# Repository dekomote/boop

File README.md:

# Boop

A small board that lets ESPHome press the power and reset buttons on a PC, and tell whether the PC is actually on.

<div style="text-align: center;">

</div>

It carries a Seeed XIAO ESP32-C3 on sockets. Two relays sit in parallel with the
front-panel power and reset buttons, so the real buttons keep working. A third
input watches the power LED header so Home Assistant knows the state instead of
guessing.

<div style="text-align: center;">

</div>

**Status:** designed and checked (ERC clean, DRC has no errors, JLCPCB's
pre-flight passes). The first board has been built and soldered, and it works.

## How it works

```
D2 (GPIO4) -> 150R -> opto -> relay K1 -> in parallel with the PWR button
D3 (GPIO5) -> 150R -> opto -> relay K2 -> in parallel with the RESET button
D1 (GPIO3) <- opto <- motherboard PWR LED header (low = PC is on)
```

- Each relay coil is switched by an LTV-817S opto (rank D, so there is enough
  gain to drive a 23 mA coil) with a 1N4148W flyback diode.
- The LED sense side is an opto with a 470R series resistor and a 10k pull-up to
  3V3. A small diode across its LED protects it if the wires are swapped.
- The board is fed 5 V either from the motherboard USB header (through a
  Schottky, so nothing flows back into the PC) or from the XIAO's own USB-C. If
  both are connected the higher one wins. One thing to avoid: the XIAO's 5 V pin
  is wired straight to USB VBUS, so if the header feeds the board while the
  USB-C is plugged into a computer that is switched off, the board pushes 5 V
  into that computer's port. Unplug the USB-C when you are done flashing.

Heads up: for the PC to be startable from off, the motherboard USB 5 V has to stay
alive in shutdown. Many boards turn it off unless you enable something like "USB
standby power" or disable ErP in the BIOS. If yours cuts it, power the board
from the USB-C instead.

## Connectors

All the 2-pin headers are 2.54 mm. The left column is always the motherboard
side and the right column is always the case side, so it is the same on every
pair.

| Ref | Label | Goes to |
|-----|-------|---------|
| J1  | 5V IN | JST XH 2-pin, `+` and `-` are marked. Optional 5 V from the motherboard USB header (pin 1 VCC, pin 7 GND) |
| J2  | PWR SW / MB | motherboard power switch header |
| J3  | PWR SW / CASE | the case power button lead |
| J4  | RST SW / MB | motherboard reset header |
| J5  | RST SW / CASE | the case reset button lead |
| J8  | PWR LED / MB | motherboard power LED header, `+` marked |
| J9  | PWR LED / CASE | the case power LED lead, `+` marked |
| J6, J7 | XIAO | 1x7 female sockets, pin names are printed on the board |

The relay contacts are volt-free, so polarity on the button headers does not
matter. The LED pair does have a polarity, follow the `+`.

Four M3 holes in the corners for standoffs.

## ESPHome

The full config is in [`boop-esphome.yaml`](boop-esphome.yaml). Pins are the XIAO
ESP32-C3 D-numbers: D1 = GPIO3, D2 = GPIO4, D3 = GPIO5.

It exposes three buttons to Home Assistant (power tap, power hold for force off,
reset) and a "PC is on" sensor. The relays are internal and always start off, so
a reboot can't hold a button down.

Create a `secrets.yaml` next to it with `wifi_ssid`, `wifi_password`,
`boop_api_key` (`openssl rand -base64 32`), `boop_ota_password` and
`boop_ap_password`, then flash the first time over USB:

```
esphome run boop-esphome.yaml
```

If the board isn't detected, hold BOOT, tap RESET, release BOOT. Unplug J1
(the motherboard 5 V) while flashing over USB-C. Later updates go over Wi-Fi.

## Building it

Everything you need for JLCPCB is in `fab/`.

## Things worth knowing

- The XIAO ESP32-C3 uses an external antenna. A metal PC case eats Wi-Fi, so
  route the antenna out of the case.
- The relays are the 4.5 V coil version (G6K-2F-Y DC4.5), on purpose. The coil
  only sees the 5 V rail minus the Schottky drop and the opto's saturation
  voltage, which is about 4.0 to 4.3 V at the USB minimum of 4.75 V (the opto's
  saturation voltage at 20-odd mA is not in the datasheet, I assumed 0.2 to
  0.4 V from the curves). A 5 V coil needs 4.0 V to pull in, which is too thin;
  the 4.5 V one pulls in at 3.6 V. Worth measuring the coil voltage on the first
  board.

## Licence

Copyright 2026 Dejan Noveski. Released under
[CC BY-SA 4.0](https://creativecommons.org/licenses/by-sa/4.0/), the full text
is in `LICENSE`. In plain words: build it, sell it, change it, as long as you
credit me and share your changes under the same licence. That covers the
schematic, the board, the Gerbers, the script and the ESPHome example.

The exception is `lib/`, which holds trimmed copies of KiCad's stock libraries.
Those keep their own licence, see `lib/NOTICE.md`.

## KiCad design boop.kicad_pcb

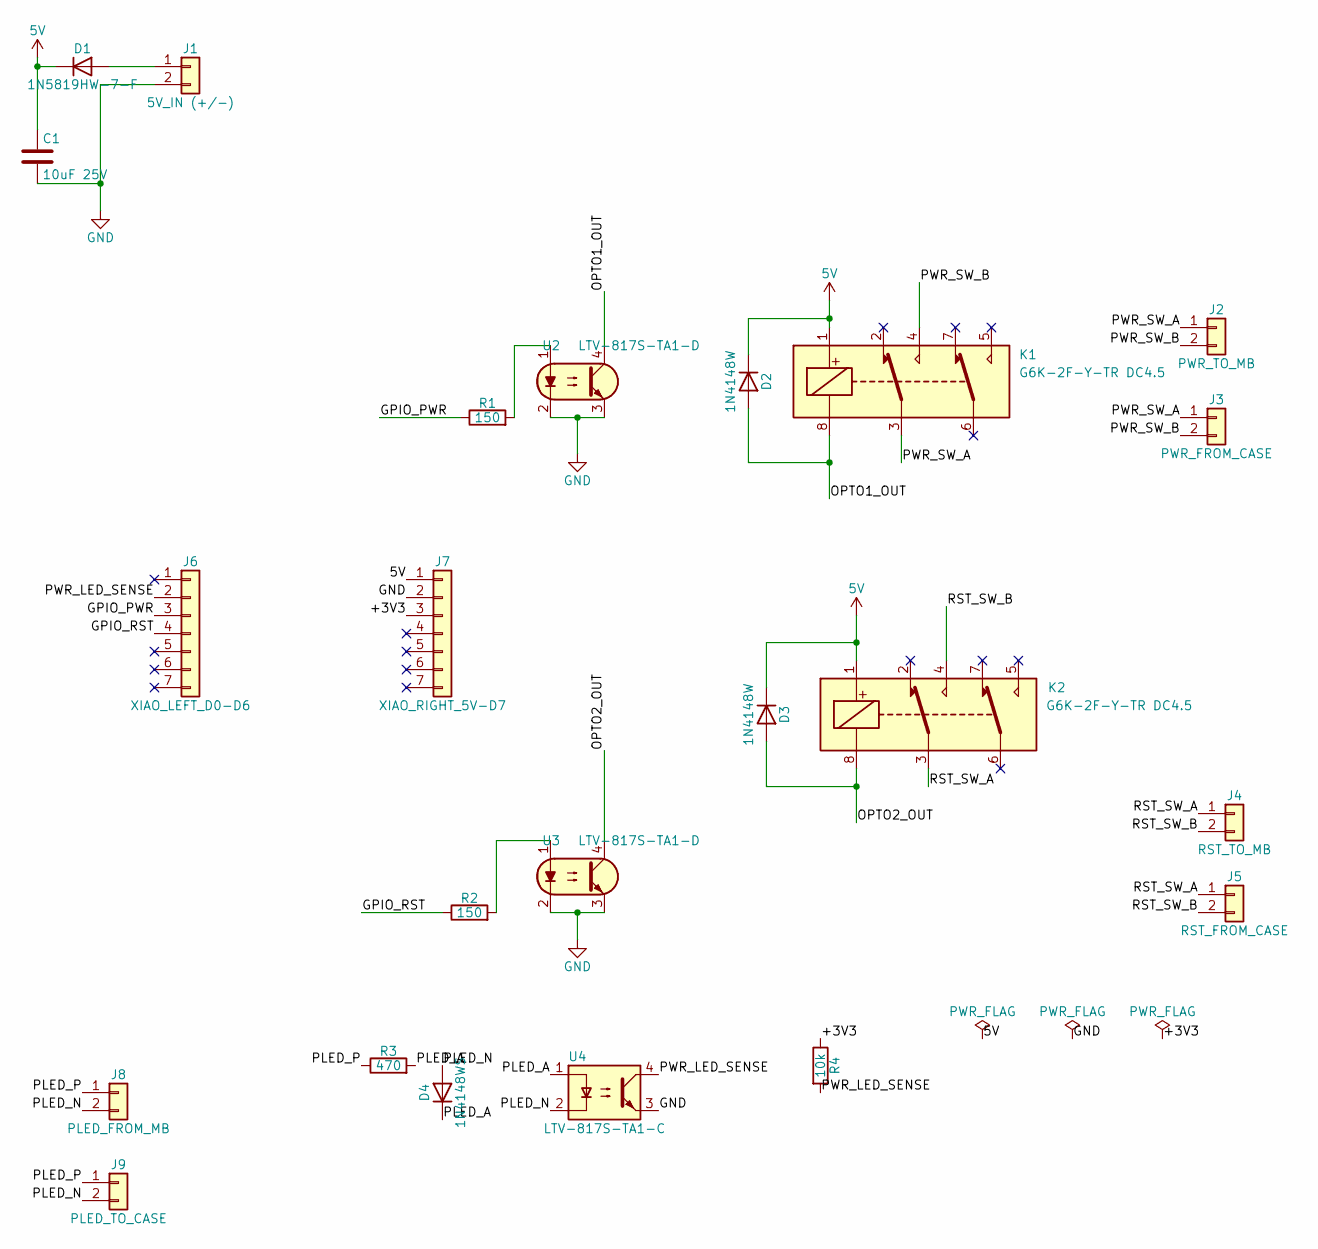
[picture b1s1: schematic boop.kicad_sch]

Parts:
C1: 10uF 25V; C_1206_3216Metric; LCSC C9807
D1: 1N5819HW-7-F; D_SOD-123; LCSC C82544
D2, D3: 1N4148W; D_SOD-123; LCSC C2099
D4: 1N4148WS; D_SOD-323; LCSC C2128
J1: 5V_IN (+/-); JST_XH_B2B-XH-A_1x02_P2.50mm_Vertical; LCSC C158012
J2: PWR_TO_MB; PinHeader_1x02_P2.54mm_Vertical; LCSC C492401
J3: PWR_FROM_CASE; PinHeader_1x02_P2.54mm_Vertical; LCSC C492401
J4: RST_TO_MB; PinHeader_1x02_P2.54mm_Vertical; LCSC C492401
J5: RST_FROM_CASE; PinHeader_1x02_P2.54mm_Vertical; LCSC C492401
J6: XIAO_LEFT_D0-D6; PinSocket_1x07_P2.54mm_Vertical; LCSC C2897370
J7: XIAO_RIGHT_5V-D7; PinSocket_1x07_P2.54mm_Vertical; LCSC C2897370
J8: PLED_FROM_MB; PinHeader_1x02_P2.54mm_Vertical; LCSC C492401
J9: PLED_TO_CASE; PinHeader_1x02_P2.54mm_Vertical; LCSC C492401
K1, K2: G6K-2F-Y-TR DC4.5; Relay_DPDT_Omron_G6K-2F-Y; LCSC C397193
R1, R2: 150; R_0603_1608Metric; LCSC C22808
R3: 470; R_0603_1608Metric; LCSC C23179
R4: 10k; R_0603_1608Metric; LCSC C25804
U2, U3: LTV-817S-TA1-D; SMDIP-4_W9.53mm; LCSC C114603
U4: LTV-817S-TA1-C; SMDIP-4_W9.53mm; LCSC C109227

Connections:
5V: C1.1, D1.1 (K), D2.1 (K), D3.1 (K), J7.1, K1.1, K2.1
/+3V3: J7.3, R4.1
/GPIO_PWR: J6.3, R1.1
/GPIO_RST: J6.4, R2.1
/OPTO1_OUT: D2.2 (A), K1.8, U2.4
/OPTO2_OUT: D3.2 (A), K2.8, U3.4
/PLED_A: D4.1 (K), R3.2, U4.1
/PLED_N: D4.2 (A), J8.2, J9.2, U4.2
/PLED_P: J8.1, J9.1, R3.1
/PWR_LED_SENSE: J6.2, R4.2, U4.4
/PWR_SW_A: J2.1, J3.1, K1.3
/PWR_SW_B: J2.2, J3.2, K1.4
/RST_SW_A: J4.1, J5.1, K2.3
/RST_SW_B: J4.2, J5.2, K2.4
GND: C1.2, J1.2, J7.2, U2.2, U2.3, U3.2, U3.3, U4.3
unnamed: D1.2 (A), J1.1
unnamed: R1.2, U2.1
unnamed: R2.2, U3.1

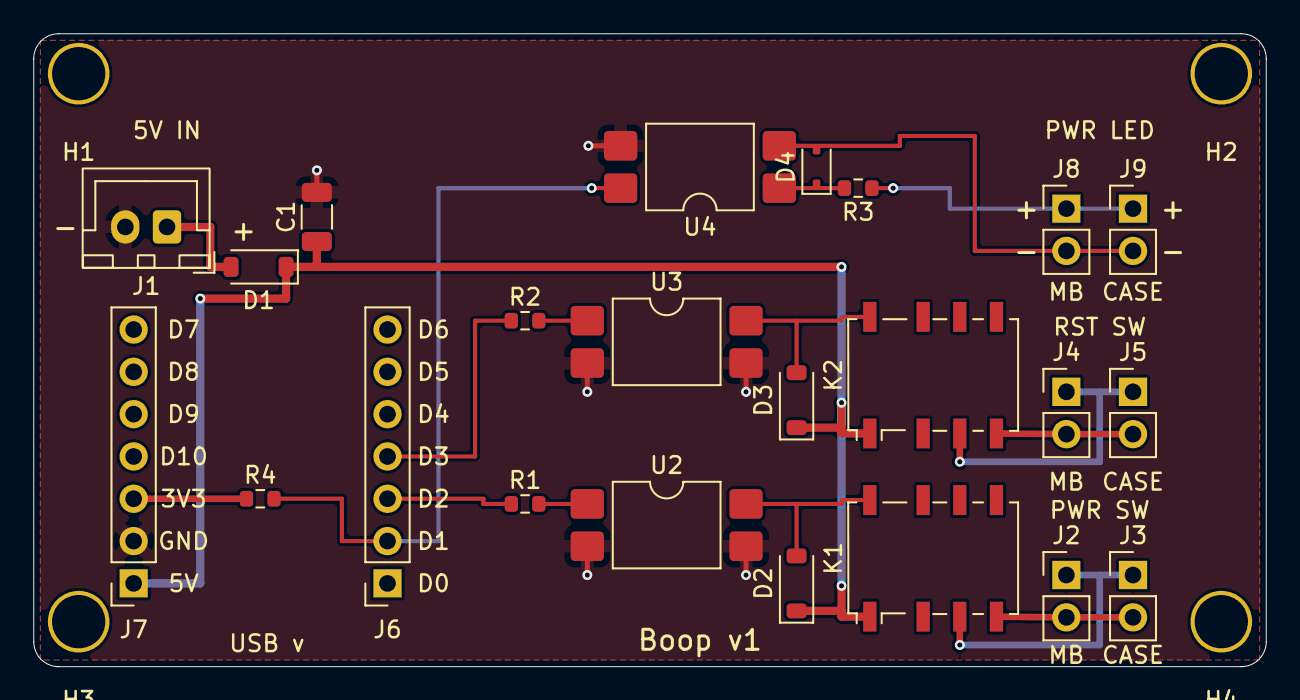
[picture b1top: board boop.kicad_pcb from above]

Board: 2 copper layers, 74.0 x 38.0 mm, 27 parts (0 on the bottom side), 18 nets.

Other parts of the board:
H1, H2, H3, H4: MountingHole; MountingHole_3.2mm

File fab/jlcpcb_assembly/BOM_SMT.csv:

"Comment","Designator","Footprint","LCSC Part #"
"10uF 25V","C1","C_1206_3216Metric","C9807"
"1N5819HW-7-F","D1","D_SOD-123","C82544"
"1N4148W","D2,D3","D_SOD-123","C2099"
"1N4148WS","D4","D_SOD-323","C2128"
"G6K-2F-Y-TR DC4.5","K1,K2","Relay_DPDT_Omron_G6K-2F-Y","C397193"
"150","R1,R2","R_0603_1608Metric","C22808"
"470","R3","R_0603_1608Metric","C23179"
"10k","R4","R_0603_1608Metric","C25804"
"LTV-817S-TA1-D","U2,U3","SMDIP-4_W9.53mm","C114603"
"LTV-817S-TA1-C","U4","SMDIP-4_W9.53mm","C109227"
